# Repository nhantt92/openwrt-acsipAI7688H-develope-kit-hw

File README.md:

# HY-AI7688H-RevA
AI7688H hardware development kit made with KiCAD

#Image

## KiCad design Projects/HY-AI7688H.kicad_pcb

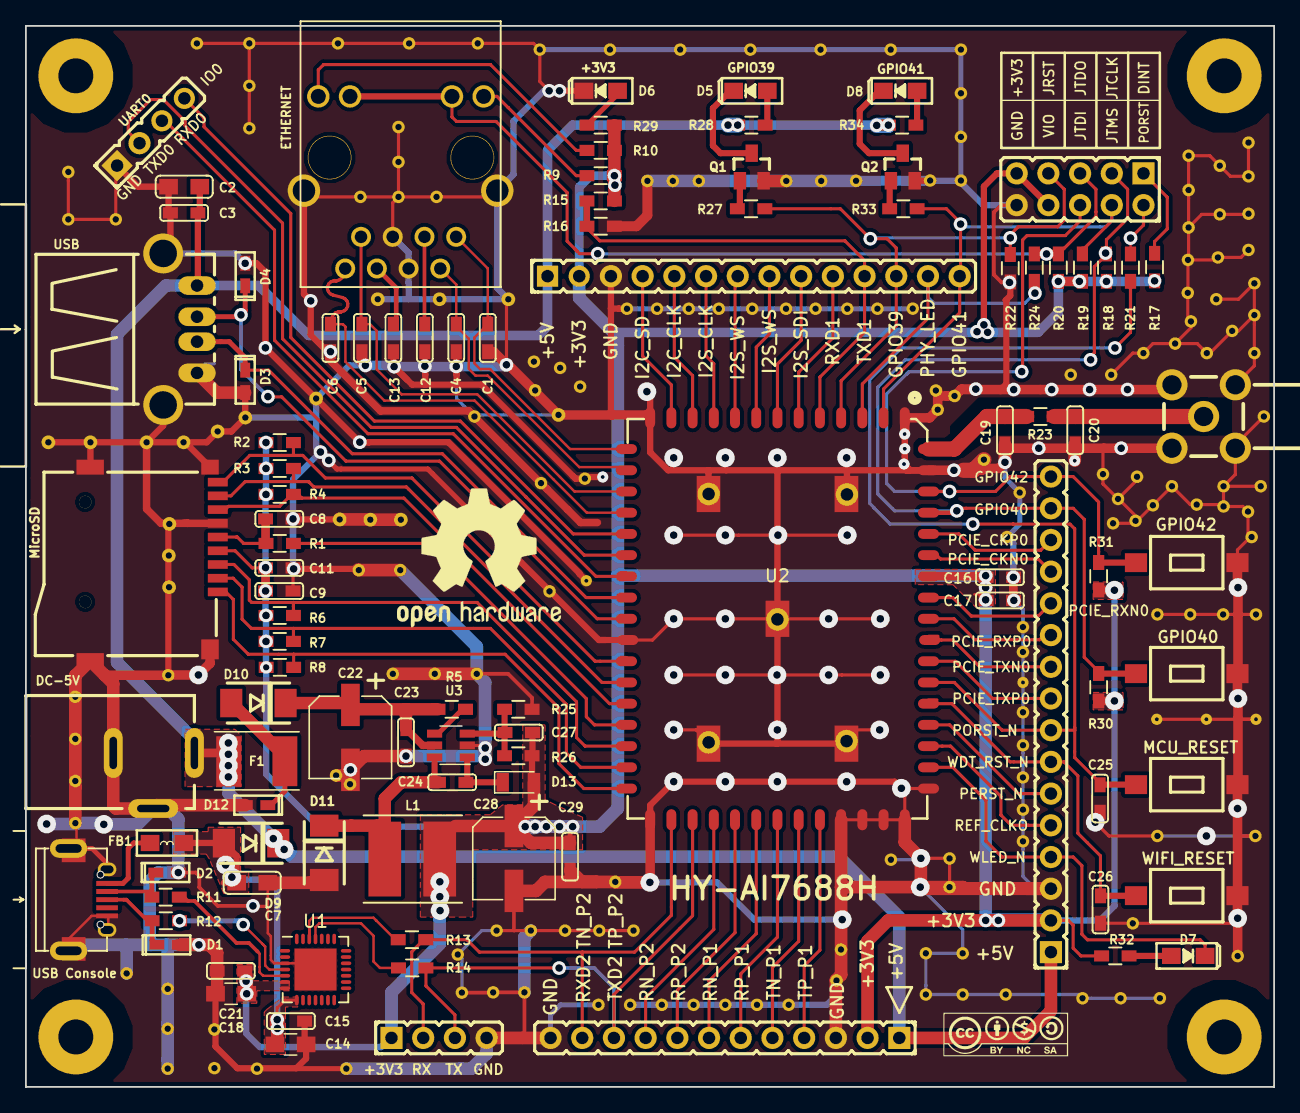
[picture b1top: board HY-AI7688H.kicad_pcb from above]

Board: 2 copper layers, 100.0 x 85.0 mm, 103 parts (0 on the bottom side), 83 nets.

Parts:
C1, C4, C5, C6, C19, C20: DNP; CAPC0603x018M
C2, C7: 10uF; CAPC0805X024M
C3, C11, C12, C13, C15, C17, C21, C23, C24, C25, C26, C27, C29: 100nF; CAPC0603x018M
C8, C9: NC; CAPC0603x018M
C14, C18: 10uF; C_0805_HandSoldering
C16: 100uF; CAPC0603x018M
C22, C28: 220uF/16V; CAPAE_6.3x7.7-M
D1, D2, D3, D4, D12: TVS; DIOC_0603X018
D5, D6, D7, D8: LED; LED_0805x024M
D9, D10, D11: D_SS24; DO-214AA
D13: D_SS24; D_SOD-323F
F1: Fuse; Fuse_SMD1812
FB1: FBM0805PT800S; FB0805x034M
J1: CONN_SMA; MOLEX_0731000114
L1: 10uH, 1.5A; Inductor_5.2x5.8x4.5
MH1, MH2, MH3, MH4: MH_32.8MM; Mounting_hole_2.8mm
MicroSD: TF-Micro-SDCard; TFC-WPAPR-08
P1: USB_OTG; USB_Micro-B_DGK609-4048-1-ND
P2: USB_A; USB_A_H_PTH
P3: HR911102A
P4: CONN_01X14; HDRV14W64_1X14_3556X254X1154
P5: CONN_01X12; HDRV12W64_1X12_3048X254X1154
P6, P10: CONN_01X04; HDRV4W64_1X4_1016X254X1154
P7: CONN_01X16; HDRV16W64_1X16_4046X254X1154
P8: CONN_02X05; HDRV10W64P254_2X5_1270X254X115P
P9: CONN-PWR-JACK; CONN_PWR_JACK_25
Q1, Q2: LMBT3904; SOT23-3-MMBT3904-M
R1, R13, R14, R21, R24: 22R; RESC0603x018M
R2, R3, R4, R6, R7, R8, R17, R30, R31: 10K; RESC0603x018M
R5: 100k; RESC0603x018M
R9, R10, R32: 330R; RESC0603x018M
R11, R12: 27R; RESC0603x018M
R15: 4.7K; RESC0603x018M
R16: DNP; RESC0603x018M
R18, R19, R20, R22: 1K; RESC0603x018M
R23: 0R; RESC0603x018M
R25: 10.5k; RESC0603x018M
R26: 33K; RESC0603x018M
R27, R33: 2.2K; RESC0603x018M
R28, R29, R34: 560R; RESC0603x018M
SW1: SW_USR1; SW-T1107A(6x3,8x2,5MM)
SW2: SW_USR2; SW-T1107A(6x3,8x2,5MM)
SW3: MPU_RESET; SW-T1107A(6x3,8x2,5MM)
SW4: WIFI_RESET; SW-T1107A(6x3,8x2,5MM)
U1: CP2102; QFN-28-1EP_5x5mm_Pitch0.5mm
U2: AI7688H; AI7688H-M
U3: LM2734Y; TSOT-23-6

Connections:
+3V3: C9.2, C11.2, C16.2, C17.2, C18.2, C21.2, C27.2, C28.1, C29.2, D13.2, L1.2, MicroSD.4, P4.2, P5.2, P7.2, P8.8, P8.9, P10.1, R2.2, R3.2, R4.2, R6.2, R7.2, R8.2, R9.1, R10.1, R15.2, R17.2, R18.2, R19.2, R20.2, R26.2, R29.2, R30.2, R31.2, R32.1, U1.6, U1.7, U2.54
+5V: C2.2, C3.2, D9.1, F1.2, P2.1, P4.1, P5.1, P7.1, P9.1, R28.2, R34.2
+5V_USBOTG: C7.2, C14.2, C15.2, D9.2, FB1.2, U1.8
/AI7688H/D+: R12.1, U1.4
/AI7688H/D-: R11.1, U1.5
/AI7688H/EJTAG_DINT: P8.1, R17.1
/AI7688H/EJTAG_PORST_N: P8.2, R21.1
/AI7688H/EPHY_LED0_N: P3.10, P3.11, P8.5, R20.1, R24.2
/AI7688H/GPIO_0: P6.4, U2.18
/AI7688H/I2C_SCLK: P4.5, U2.11
/AI7688H/I2C_SD: P4.4, U2.12
/AI7688H/I2S_SCLK: P4.6, U2.10
/AI7688H/I2S_SDI: P4.9, U2.7
/AI7688H/I2S_SDO: P4.8, U2.8
/AI7688H/I2S_WS: P4.7, U2.9
/AI7688H/JRST_GPIO_39: P4.12, P8.7, R22.2, R27.1, U2.4
/AI7688H/JTCLK_GPIO_40: P7.15, P8.3, R18.1, R30.1, SW2.1, U2.57
/AI7688H/JTDI_GPIO_42: P7.16, P8.6, R31.1, SW1.1, U2.58
/AI7688H/JTDO_EPHY_LED0_N: P4.13, R24.1, U2.3
/AI7688H/JTMS_GPIO_41: P4.14, P8.4, R19.1, R33.1, U2.2
/AI7688H/MDI_P0_R_N: C4.2, P3.2, U2.15
/AI7688H/MDI_P0_R_P: C1.2, P3.1, U2.14
/AI7688H/MDI_P0_T_N: C6.2, P3.8, U2.17
/AI7688H/MDI_P0_T_P: C5.2, P3.7, U2.16
/AI7688H/MDI_RN_P1: P5.7, U2.36
/AI7688H/MDI_RN_P2: P5.9, U2.34
/AI7688H/MDI_RN_P3: MicroSD.7, R4.1, U2.26
/AI7688H/MDI_RN_P4: MicroSD.3, R6.1, U2.28
/AI7688H/MDI_RP_P1: P5.6, U2.37
/AI7688H/MDI_RP_P2: P5.8, U2.35
/AI7688H/MDI_RP_P3: MicroSD.8, R3.1, U2.25
/AI7688H/MDI_RP_P4: R1.1, U2.27
/AI7688H/MDI_TN_P1: P5.5, U2.38
/AI7688H/MDI_TN_P2: P5.11, P10.2, R13.1, U2.32
/AI7688H/MDI_TN_P3: MicroSD.9, R2.1, U2.24
/AI7688H/MDI_TN_P4: MicroSD.1, R8.1, U2.30
/AI7688H/MDI_TP_P1: P5.4, U2.39
/AI7688H/MDI_TP_P2: P5.10, P10.3, R14.1, U2.33
/AI7688H/MDI_TP_P4: MicroSD.2, R7.1, U2.29
/AI7688H/PCIE_CK0_N: P7.13, U2.55
/AI7688H/PCIE_CK0_P: P7.14, U2.56
/AI7688H/PCIE_RX0_N: P7.12, U2.53
/AI7688H/PCIE_RX0_P: P7.11, U2.52
/AI7688H/PCIE_TX0_N: P7.10, U2.51
/AI7688H/PCIE_TX0_P: P7.9, U2.50
/AI7688H/PERST_N: P7.6, U2.47
/AI7688H/PORST_N: C25.1, P7.8, R21.2, SW3.1, U2.49
/AI7688H/REF_CLKO: P7.5, U2.46
/AI7688H/RF: C19.2, R23.2, U2.60
/AI7688H/UART_7688_RXD0: P6.3, U2.20
/AI7688H/UART_7688_RXD1: P4.10, U2.6
/AI7688H/UART_7688_TXD0: P6.2, U2.19
/AI7688H/UART_7688_TXD1: P4.11, R15.1, R16.2, U2.5
/AI7688H/USB_D_N: D4.1, P2.2, U2.22
/AI7688H/USB_D_P: D3.1, P2.3, U2.21
/AI7688H/WDT_RST_N: C26.1, P7.7, SW4.1, U2.48
/AI7688H/WLED_N: D7.1, P7.4, U2.45
GND: C1.1, C2.1, C3.1, C4.1, C5.1, C6.1, C7.1, C8.1, C9.1, C11.1, C12.1, C13.1, C14.1, C15.1, C16.1, C17.1, C18.1, C19.1, C20.1, C21.1, C22.2, C23.1, C25.2, C26.2, C28.2, C29.1, D1.2, D2.2, D3.2, D4.2, D6.1, D11.2, D12.2, J1.2, J1.3, J1.4, J1.5, MicroSD.6, MicroSD.10, MicroSD.11, MicroSD.12, MicroSD.13, P1.5, P1.6, P2.4, P2.5, P3.4, P3.5, P3.13, P3.14, P4.3, P5.3, P5.12, P6.1, P7.3, P8.10, P9.2, P9.3, P10.4, Q1.2, Q2.2, R16.1, R22.1, R25.1, SW1.2, SW2.2, SW3.2, SW4.2, U1.3, U1.29, U2.1, U2.13, U2.23, U2.31, U2.40, U2.41, U2.42, U2.43, U2.44, U2.59, U2.61, U2.62, U2.63, U2.64, U2.65, U3.2
unnamed: C8.2, MicroSD.5, R1.2
unnamed: C12.2, P3.3
unnamed: C13.2, P3.6
unnamed: C20.2, J1.1, R23.1
unnamed: C22.1, C23.2, D10.1, R5.1, U3.5
unnamed: C24.1, D13.1, U3.1
unnamed: C24.2, D11.1, L1.1, U3.6
unnamed: C27.1, R25.2, R26.1, U3.3
unnamed: D1.1, P1.3, R12.2
unnamed: D2.1, P1.2, R11.2
unnamed: D5.1, Q1.3
unnamed: D5.2, R28.1
unnamed: D6.2, R29.1
unnamed: D7.2, R32.2
unnamed: D8.1, Q2.3
unnamed: D8.2, R34.1
unnamed: D10.2, D12.1, F1.1
unnamed: FB1.1, P1.1
unnamed: P3.9, R9.2
unnamed: P3.12, R10.2
unnamed: Q1.1, R27.2
unnamed: Q2.1, R33.2
unnamed: R5.2, U3.4
unnamed: R13.2, U1.26
unnamed: R14.2, U1.25

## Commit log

2019-03-08 upload project
2019-05-31 fix footprint cp2102
